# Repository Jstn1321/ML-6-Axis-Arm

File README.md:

<h1 align="center">JN V1</h1>

<h4 align="center">A 3D printable 6-axis robotic arm with computer vision</h4>

<h1></h1>

<p align="center">
  <a href="#assembly">Assembly</a> •
  <a href="#how-to-use">How To Use</a> • 
  <a href="#demo">Demo</a> •
  <a href="#photoshoot">Photoshoot</a> •
  <a href="#credits">Credits</a>
</p>

# **Assembly**

_Under construction_

# **How to use**

<h3> For Manual Control</h3>

1. Launch up the app and ensure the camera is connected to the computer
2. Select the manual button on the sidebar and use the joysticks to control each joint on the robot

<h3> For Automatic Control</h3>

1. Launch up the app and ensure the camera is connected to the computer
2. Select the automatic button on the sidebar
3. Press the "Take a Picture" Button to grab a picture of the items you want to sort
4. Select "Identify" for object recognition
 
5. Select "Sort" to make the arm sort all the objects

   It should print out inverse kinemetics and the robot arm should begin to move

# **Demo**
Watch the robot arm sort two boxes:

# **Photoshoot**

# **Credits**

- [Chris Annin](https://www.anninrobotics.com/) for his work on his [AR4 Robot](https://www.youtube.com/watch?v=iB2NAgfVjIs&t=90s) which inspired me for many of my design choices.
  
- [Code Commerce](https://www.youtube.com/@codecommerce) for his design on the [interactive sidebar](https://www.youtube.com/watch?v=uy1tgKOnPB0) which is probably the coolest part of the GUI.

- [Tyler Potts](https://www.youtube.com/@TylerPotts) for his cool [button design](https://github.com/TylerPottsDev/yt-css-buttons) which was used generously in the GUI.

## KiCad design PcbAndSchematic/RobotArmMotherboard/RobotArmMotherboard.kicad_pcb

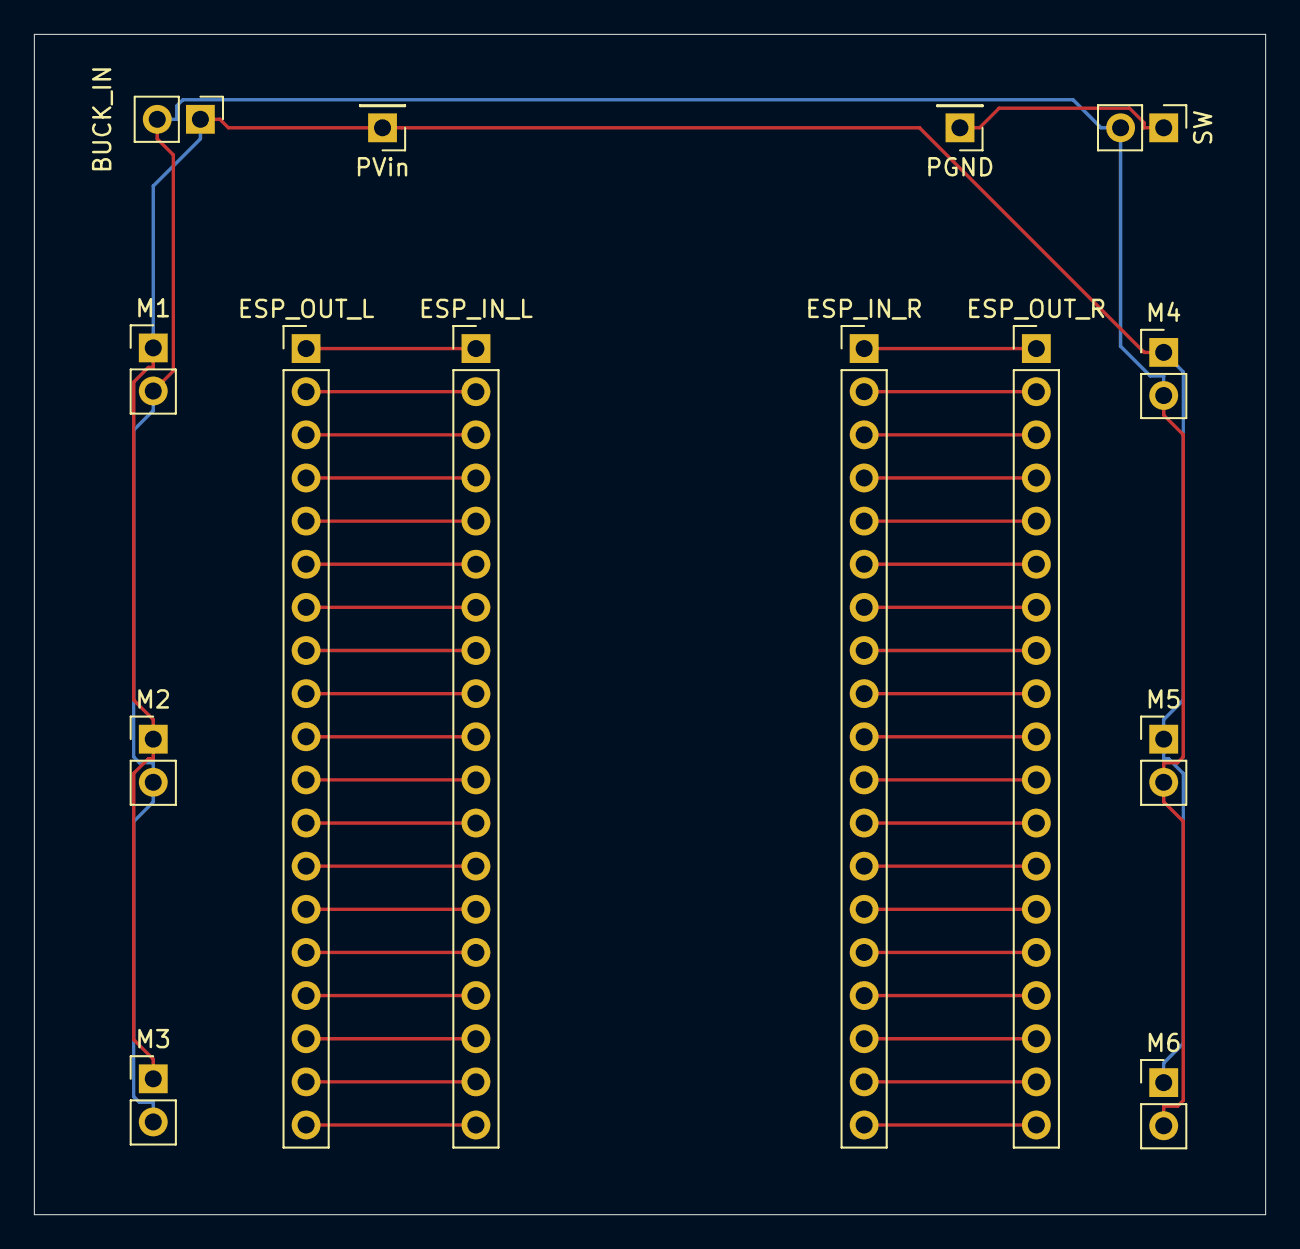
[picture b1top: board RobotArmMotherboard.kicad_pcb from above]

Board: 2 copper layers, 72.5 x 69.5 mm, 14 parts (0 on the bottom side), 41 nets.

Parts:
BUCK_IN: 24v to 5v for buck converter; PinHeader_1x02_P2.54mm_Vertical
ESP_IN_L: Conn_01x19_Socket; PinHeader_1x19_P2.54mm_Vertical
ESP_IN_R: Conn_01x19_Socket; PinHeader_1x19_P2.54mm_Vertical
ESP_OUT_L: Conn_01x19_Pin; PinHeader_1x19_P2.54mm_Vertical
ESP_OUT_R: Conn_01x19_Pin; PinHeader_1x19_P2.54mm_Vertical
M1, M2, M3, M4, M5, M6: Conn_01x02_Pin; PinHeader_1x02_P2.54mm_Vertical
PGND: GND; PinHeader_1x01_P2.54mm_Vertical
PVin: 24V @5A; PinHeader_1x01_P2.54mm_Vertical
SW: SW_SPST; PinHeader_1x02_P2.54mm_Vertical

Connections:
unnamed: BUCK_IN.1, M1.1, M2.1, M3.1, M4.1, M5.1, M6.1, PVin.1
unnamed: BUCK_IN.2, M1.2, M2.2, M3.2, M4.2, M5.2, M6.2, SW.2 (B)
unnamed: ESP_IN_L.1, ESP_OUT_L.1
unnamed: ESP_IN_L.2, ESP_OUT_L.2
unnamed: ESP_IN_L.3, ESP_OUT_L.3
unnamed: ESP_IN_L.4, ESP_OUT_L.4
unnamed: ESP_IN_L.5, ESP_OUT_L.5
unnamed: ESP_IN_L.6, ESP_OUT_L.6
unnamed: ESP_IN_L.7, ESP_OUT_L.7
unnamed: ESP_IN_L.8, ESP_OUT_L.8
unnamed: ESP_IN_L.9, ESP_OUT_L.9
unnamed: ESP_IN_L.10, ESP_OUT_L.10
unnamed: ESP_IN_L.11, ESP_OUT_L.11
unnamed: ESP_IN_L.12, ESP_OUT_L.12
unnamed: ESP_IN_L.13, ESP_OUT_L.13
unnamed: ESP_IN_L.14, ESP_OUT_L.14
unnamed: ESP_IN_L.15, ESP_OUT_L.15
unnamed: ESP_IN_L.16, ESP_OUT_L.16
unnamed: ESP_IN_L.17, ESP_OUT_L.17
unnamed: ESP_IN_L.18, ESP_OUT_L.18
unnamed: ESP_IN_L.19, ESP_OUT_L.19
unnamed: ESP_IN_R.1, ESP_OUT_R.1
unnamed: ESP_IN_R.2, ESP_OUT_R.2
unnamed: ESP_IN_R.3, ESP_OUT_R.3
unnamed: ESP_IN_R.4, ESP_OUT_R.4
unnamed: ESP_IN_R.5, ESP_OUT_R.5
unnamed: ESP_IN_R.6, ESP_OUT_R.6
unnamed: ESP_IN_R.7, ESP_OUT_R.7
unnamed: ESP_IN_R.8, ESP_OUT_R.8
unnamed: ESP_IN_R.9, ESP_OUT_R.9
unnamed: ESP_IN_R.10, ESP_OUT_R.10
unnamed: ESP_IN_R.11, ESP_OUT_R.11
unnamed: ESP_IN_R.12, ESP_OUT_R.12
unnamed: ESP_IN_R.13, ESP_OUT_R.13
unnamed: ESP_IN_R.14, ESP_OUT_R.14
unnamed: ESP_IN_R.15, ESP_OUT_R.15
unnamed: ESP_IN_R.16, ESP_OUT_R.16
unnamed: ESP_IN_R.17, ESP_OUT_R.17
unnamed: ESP_IN_R.18, ESP_OUT_R.18
unnamed: ESP_IN_R.19, ESP_OUT_R.19
unnamed: PGND.1, SW.1 (A)

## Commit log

2024-07-24 Create d
2024-07-24 Create e
2024-07-24 Create Rpi4Code
2024-11-28 added a roller tapered bearing design on the elbow y axis, elbow x axis, wrist y axis joints, added screw caps on the shoulder y and x axis to hide screws, added cable management threads, improved sh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
2024-11-28 Created README.md
2024-11-28 Added pictures for readme
2024-11-28 Uploaded some photos for readme and tried to get the arduino mega to work for the motherboard, didnt work still
2024-11-28 Photos for readme
2024-11-29 Added photo
2024-12-01 FINALLY FIXED ARDUINO CODE SO STEPPER MOTORS NOW RUN AT NORMAL SPEEDS
2024-12-01 Increased diameter
2024-12-01 Lowered speed for J2 motor on manual control
2024-12-01 literally did nothing
2024-12-03 Added case for electrical components
2024-12-11 Added OLED status displace and RGB led indicator
2024-12-11 added some photos
2024-12-15 Added mounting bracket for OLED screen and RGB indicator light
2024-12-22 Cleaned up directory
2024-12-23 Created URDF file for inverse kine
2024-12-23 Added inverse/forward kine python script
2024-12-23 Updated to Solidworks 2025
2024-12-24 Made it so that the units are in meters and not in milimeters
2024-12-24 Added a callable function and made sure the inverse kinematics were somewhat similar to its forward kinematics
2024-12-24 Made a main file
2024-12-24 Moved to code folder
2024-12-29 Added a gitignore
2024-12-29 Made the function return a list not a numpy list
2024-12-29 Changed name to ArduinoMegaCode
2024-12-29 Added two-way communication with pc and arduino
2024-12-29 Added files needed for electron
2024-12-29 Moved to App Folder
2024-12-29 Added a cool little sidebar for switching modes
2024-12-30 Changed # of steps per epoch, # of epochs to match the samples to hopefully improve the model
2024-12-30 Hopefully a more accurate model
2024-12-30 Ignore filename.jpg
2024-12-30 Added scripts so it runs when you press the button
2024-12-30 Deleted useless files
2024-12-30 Added buttons for automatic tab and a console box
2024-12-30 Enlarged the window so it can fit the console
2024-12-30 Removed Some Useless Comments
2024-12-31 Moved to a more appropriate spot
2024-12-31 Tried to get buttons to activate script (dosen't work yet)
2024-12-31 Added the code from ApplyModel to the scripts so they can be run through button press
2024-12-31 Now when you press button it runs the python script and prints its output in the console
2024-12-31 Modified print statements and paths to work with the electron app
2025-01-03 Added script to tell arduino its on the auto mode
2025-01-03 Added script to tell the arduino its on the manual mode
2025-01-03 Somewhat added a way to send the arduino inv kine angles according to the ai models readings
2025-01-03 Made this script only send messages
2025-01-03 Made the function make the end effector point downward so it can actually pick up stuff
2025-01-03 idk why soldiworks made these files but im just going to commit it because I dont want an annoying icon bugging me
2025-01-03 Deleted pcb folder because I don't need a pcb
2025-01-03 Deleted useless excel spreadsheet for I am no longer using esp32s.
2025-01-03 Added a folder to store all previous designs to make the CAD folder make more sense
2025-01-03 Deleted all unnecessary files
2025-01-03 Deleted FinalRobotArmCADModels because why have a folder like that when you have a CAD folder
2025-01-05 Runs auto or manual script to change the mode on the arduino
2025-01-05 Reads the data being sent from the python scripts and changes mode accordingly
2025-01-05 Fixed window height
2025-01-07 Changed background color and made buttons bigger
2025-01-12 Added python script that combines all other scripts into one
2025-01-12 Added another button
2025-01-12 Changed the height of the buttons to fit all four and added another button
2025-01-20 Created YOLOV11 Models for faster and more accurate inference
2025-01-21 Add gitignore
2025-01-21 Buttons use the new yolo model scripts
2025-01-21 Uses a custom yolov11 model to identify boxes instead of my custom tensorflow model
2025-01-21 Use yolo models output to sort boxes
2025-01-21 Save the output in a json file for sortYOLO.py to use
2025-01-21 YOLOV11 model
2025-01-21 Test script for the yolo model
2025-01-21 Update gitignore
2025-01-21 Converted radians to degrees and converted to number of steps for each motor
2025-01-25 Increased height to not crush the limit switch
2025-01-25 Added single box feedback
2025-01-25 Ignore boxCoords.json
2025-01-25 Update Displayed Image
2025-01-25 Update image with annotated image
2025-01-25 Fixed print error
2025-01-25 Commit so vs code will stop bothering me
2025-01-25 Fixed wrong gear ratios
2025-01-25 Added calibration functions for each motor (still need to find perfect values
2025-01-27 Increased the height so the arm isn't resting on the limit switch
2025-01-28 Changed Height to not mess with the limit switch
2025-01-30 FIxed OLED and LED bug, changed speeds for motors
2025-02-09 A lot of progress with this one commit since the calibration code is finished (for one motor but it is the same for all others)
2025-02-10 Fixed bug where it wouldnt run through the while loop because I set acceleration and max speed value for some reason
2025-02-10 Removed the bug testing lines of code
2025-02-12 Tested and completed code for calibration for J2,J4,J5,J6. J1 i havent installed limit switch yet and J3 I just didn't have time.
2025-02-13 Added a second floor for the arduino
2025-02-13 Removed the need for a conda environment
2025-02-13 Limit switch now works for L3, also changed the speeds so it wont be as fast (which is good)
2025-02-15 Added limits
2025-02-16 Updated gitIgnore
2025-02-16 Can now send inverse kine to arduino and it will move the motors according to what is sent to it
2025-02-16 Added a new line to the message
2025-02-16 Just changed camera index
2025-02-16 Checks if there is a blue/green box to prevent error
2025-02-16 Changed nothing
2025-02-16 Add to github so it will stop bothering me
2025-02-16 Added some troubleshooting print statements and added a VERY IMPORTANT comment to show me what is xyz for the ik function since the documentation for the function kinda sucks
2025-02-16 Added the offsets to link with the invKine functions and the axis of the arm
2025-02-16 Commit so vs code can leave me alone
2025-02-18 Now we only send degrees instead of steps because of integer issues
2025-02-18 Modifed for a better way to send data to teh arduino
2025-02-18 Added a header so the arduino can better distinguish between the inverse kine list and when to switch from auto and manual
2025-02-18 Added another parameter so it can tell the arduino if its a green or blue box
2025-02-18 Added a smaller upper limit since the limit switch blocks the motor from reaching 3.14 anyways
2025-02-18 Added multistepper features which seem to not be working for some reason, also made the communication between the pc and the arduino a lot more accurate, fixed a lot of bugs with the types of variabl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
2025-02-19 Added servo object, and added the lists of steps to reach the sorted positions of the green and blue boxes
2025-02-19 Fullly added the sorting code
2025-02-19 Changed the positions of steps to reflect the actual positions
2025-02-19 Did it to the green list aswell
2025-02-20 Now the ik function returns the steps instead of just the degrees leading to even more accurate values
2025-02-20 This now sends long values to account for the fact that the ik function sends long values
2025-02-20 Slighly changed the steps to get to blueSorted and greenSorted, also modified the logic to recieve values from the python script to accept long values, and now the gotoposition gets values through a 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
2025-02-20 Made the limit more accurate to real life
2025-02-20 Added a distancer to keep the 0.25m constant
2025-02-20 Added a thicker section to the end of it to keep it installed in the gripper
2025-02-21 Create LICENSE
2025-02-21 Added some better print statemens just for readability
2025-02-21 Removed the useless import of invKine.py
2025-02-21 Just added more helpful debugging prints
2025-02-21 Added servo functionality, changed the speeds of the motors and the shortened the delay between going to positions
2025-02-21 Removed old asm
2025-02-21 Created the new final robot arm asm
2025-02-21 Updated to sw 2025
2025-04-02 Cover for elbow for the science fair
2025-04-02 Cover for the belt on the wrist for the science fair
2025-04-02 Made a part to put some pressure on the belt to maybe reduce the belt slip
2025-04-02 A much better belt tensioner which utilizes bearings to make a tighter belt
2025-04-02 Changed the offset amount on the z axis by 8cm
2025-04-03 Updated gitingnore
2025-06-06 Put all tensorflow folders into one tensorflow folder for organization
2025-06-06 Put all YOLO folders into one YOLO folder for organization
